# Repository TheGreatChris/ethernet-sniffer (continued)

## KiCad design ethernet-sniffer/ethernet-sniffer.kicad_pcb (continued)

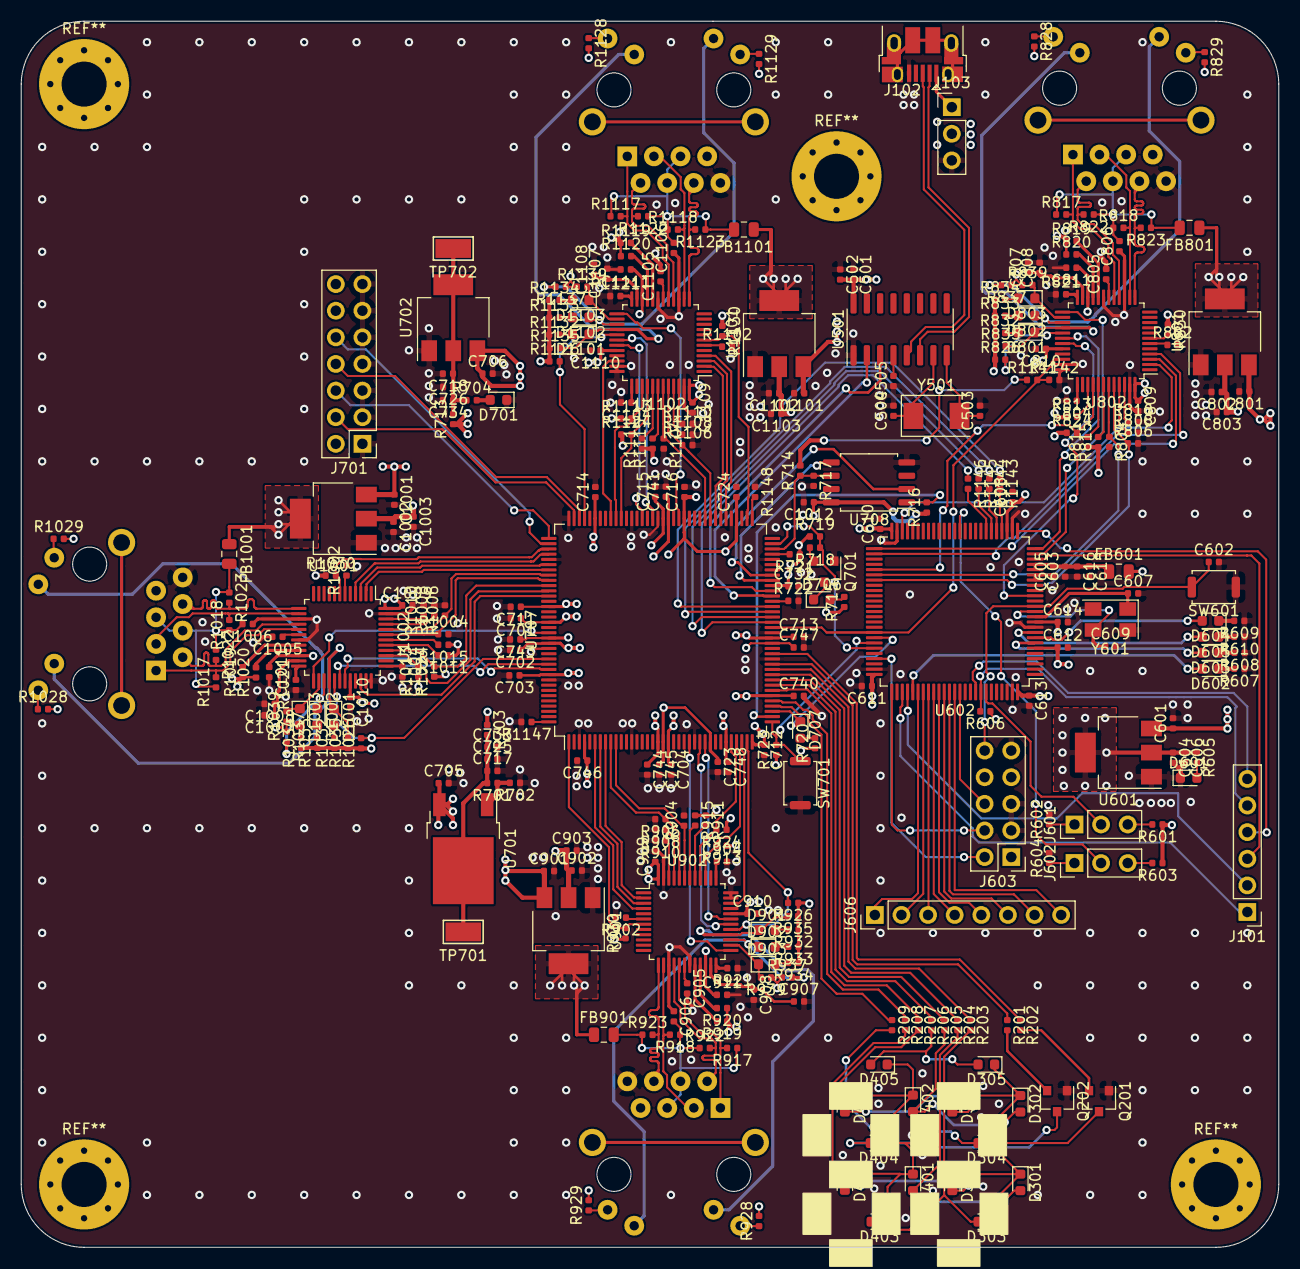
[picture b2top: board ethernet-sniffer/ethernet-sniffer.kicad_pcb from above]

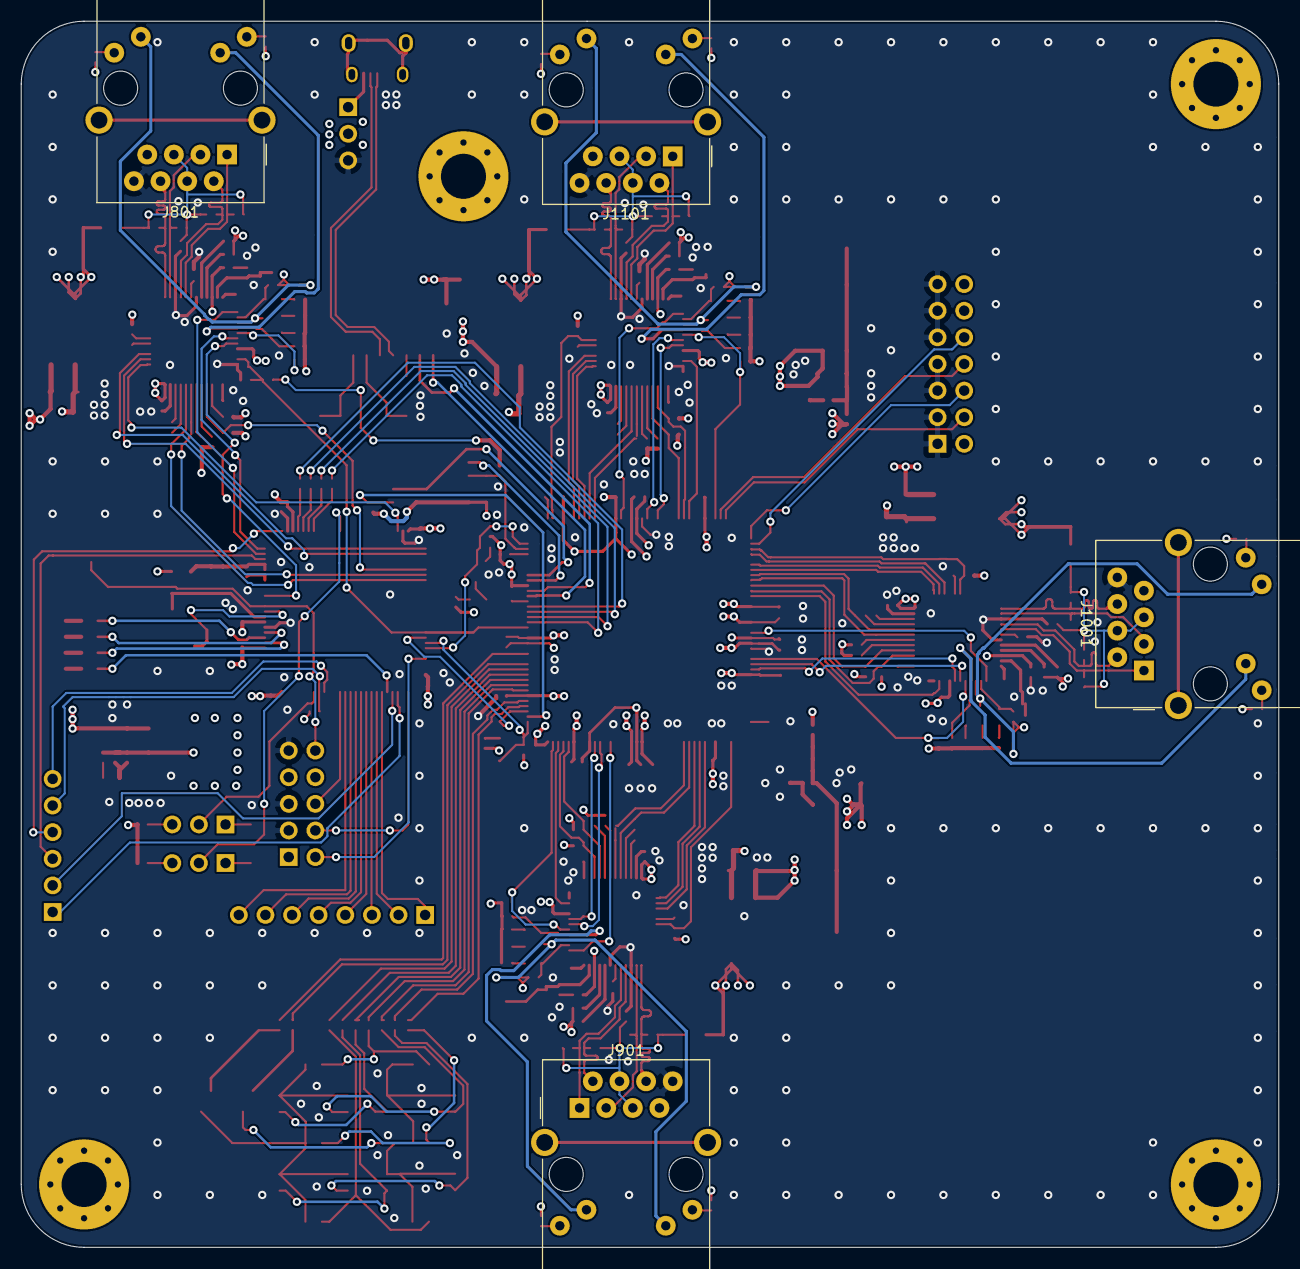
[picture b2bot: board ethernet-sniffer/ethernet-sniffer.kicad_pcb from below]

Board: 4 copper layers, 120.0 x 117.0 mm, 316 parts (4 on the bottom side), 252 nets.

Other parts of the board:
D301, D401: B; LED_0603_1608Metric
D302, D402: C; LED_0603_1608Metric
D303, D403: A; LED_0603_1608Metric
D304, D404: G; LED_0603_1608Metric
D305, D405: D; LED_0603_1608Metric
D306, D406: F; LED_0603_1608Metric
D307, D407: E; LED_0603_1608Metric
Q201, Q202: 2N3904; SOT-23
R201, R202: 1k; R_0402_1005Metric
R203, R204, R205, R206, R207, R208, R209: 200; R_0402_1005Metric

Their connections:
/7seg-display/7SEG-1: R201.1; also elsewhere on the board
/7seg-display/7SEG-2: R202.1; also elsewhere on the board
/7seg-display/7SEG-A: R203.1; also elsewhere on the board
/7seg-display/7SEG-B: R204.1; also elsewhere on the board
/7seg-display/7SEG-C: R205.1; also elsewhere on the board
/7seg-display/7SEG-D: R206.1; also elsewhere on the board
/7seg-display/7SEG-E: R207.1; also elsewhere on the board
/7seg-display/7SEG-F: R208.1; also elsewhere on the board
/7seg-display/7SEG-G: R209.1; also elsewhere on the board
/7seg-display/Digit 1/AK: D301.1, D302.1, D303.1, D304.1, D305.1, D306.1, D307.1, Q201.3
/7seg-display/Digit 1/AN: D303.2, D403.2, R203.2
/7seg-display/Digit 1/BA: D301.2, D401.2, R204.2
/7seg-display/Digit 1/CA: D302.2, D402.2, R205.2
/7seg-display/Digit 1/DA: D305.2, D405.2, R206.2
/7seg-display/Digit 1/EA: D307.2, D407.2, R207.2
/7seg-display/Digit 1/FA: D306.2, D406.2, R208.2
/7seg-display/Digit 1/GA: D304.2, D404.2, R209.2
/7seg-display/Digit 2/AK: D401.1, D402.1, D403.1, D404.1, D405.1, D406.1, D407.1, Q202.3
GNDD: Q201.1, Q202.1; also elsewhere on the board
unnamed: Q201.2, R202.2
unnamed: Q202.2, R201.2

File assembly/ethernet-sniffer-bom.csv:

Comment,Designator,Footprint,LCSC Part #
100n,"C501,C505,C608,C610,C611,C612,C613,C602,C804,C805,C807,C803,C806,C809,C810,C811,C904,C905,C907,C903,C906,C909,C910,C911,C1104,C1105,C1107,C1103,C1106,C1109,C1110,C1111,C741,C743,C745,C747,C702,C704,C712,C713,C715,C701,C703,C711,C714,C716,C724,C732,C740,C744,C746,C748,C723,C1012,C1004,C1005,C1007,C1003,C1006,C1009,C1010,C1011",Capacitor_SMD:C_0402_1005Metric,C1525
10n,"C502,C615,C605",Capacitor_SMD:C_0402_1005Metric,C15195
33p,"C504,C503",Capacitor_SMD:C_0402_1005Metric,C1562
10u,"C601,C604,C808,C801,C908,C901,C1108,C1101,C717,C718,C1008,C1001",Capacitor_SMD:C_0402_1005Metric,C15525
1u,"C606,C616,C603,C802,C902,C1102,C1002",Capacitor_SMD:C_0402_1005Metric,C52923
12p,"C607,C609",Capacitor_SMD:C_0402_1005Metric,C1547
4u7,"C614,C705,C725,C706,C726",Capacitor_SMD:C_0402_1005Metric,C23733
470n,"C733,C734",Capacitor_SMD:C_0402_1005Metric,C47339
B,"D301,D401",LED_SMD:LED_0603_1608Metric,C2286
C,"D302,D402",LED_SMD:LED_0603_1608Metric,C2286
A,"D303,D403",LED_SMD:LED_0603_1608Metric,C2286
G,"D304,D404",LED_SMD:LED_0603_1608Metric,C2286
D,"D305,D405",LED_SMD:LED_0603_1608Metric,C2286
F,"D306,D406",LED_SMD:LED_0603_1608Metric,C2286
E,"D307,D407",LED_SMD:LED_0603_1608Metric,C2286
LED STM POW,D601,LED_SMD:LED_0603_1608Metric,C2286
LED_Small,"D602,D603,D604,D605,D701",LED_SMD:LED_0603_1608Metric,C2286
INIT,"D707,D706",LED_SMD:LED_0603_1608Metric,C2286
LINK,"D801,D901,D1101,D1001",LED_SMD:LED_0603_1608Metric,C2286
SPEED,"D802,D902,D1102,D1002",LED_SMD:LED_0603_1608Metric,C2286
ACT,"D803,D903,D1103,D1003",LED_SMD:LED_0603_1608Metric,C2286
Bead,"FB601,FB801,FB901,FB1101,FB1001",Inductor_SMD:L_0805_2012Metric,C1017
2N3904,"Q202,Q201,Q701",Package_TO_SOT_SMD:SOT-23,C18536
1k,"R201,R202,R1143,R1144,R1145,R1146",Resistor_SMD:R_0402_1005Metric,C11702
200,"R203,R204,R205,R206,R207,R208,R209,R605,R607,R608,R609,R610,R832,R833,R834,R828,R829,R932,R933,R934,R928,R929,R1132,R1133,R1134,R1128,R1129,R704,R720,R715,R716,R1032,R1033,R1034,R1028,R1029",Resistor_SMD:R_0402_1005Metric,C25087
10k,"R602,R601,R604,R603,R718",Resistor_SMD:R_0402_1005Metric,C25744
2k2,"R606,R819,R820,R802,R804,R806,R808,R810,R811,R813,R815,R824,R826,R830,R835,R837,R839,R919,R920,R902,R904,R906,R908,R910,R911,R913,R915,R924,R926,R930,R935,R937,R939,R1119,R1120,R1102,R1104,R1106,R1108,R1110,R1111,R1113,R1115,R1124,R1126,R1130,R1135,R1137,R1139,R719,R721,R722,R723,R1147,R1148,R1019,R1020,R1002,R1004,R1006,R1008,R1010,R1011,R1013,R1015,R1024,R1026,R1030,R1035,R1037,R1039",Resistor_SMD:R_0402_1005Metric,C25879
0,"R701,R703,R713",Resistor_SMD:R_0402_1005Metric,C17168
1M,R702,Resistor_SMD:R_0402_1005Metric,C26083
100,"R717,R714,R1141,R1142",Resistor_SMD:R_0402_1005Metric,C25076
50,"R818,R823,R817,R822,R918,R923,R917,R922,R1118,R1123,R1117,R1122,R1018,R1023,R1017,R1022",Resistor_SMD:R_0402_1005Metric,C25120
4k87,"R821,R921,R1121,R1021",Resistor_SMD:R_0402_1005Metric,C25900
CH340G,U501,Package_SO:SOIC-16_3.9x9.9mm_P1.27mm,C14267
AMS1117-3.3,"U601,U801,U901,U1101,U702,U1001",Package_TO_SOT_SMD:SOT-223-3_TabPin2,C6186
STM32F107VCTx,U602,Package_QFP:LQFP-100_14x14mm_P0.5mm,C8315
LM317_3PinPackage,U701,Package_TO_SOT_SMD:TO-252-2,C75510
XC6SLX9-TQG144,U707,Package_QFP:LQFP-144_20x20mm_P0.5mm,C27408
W25Q128JVS,U708,Package_SO:SOIC-8_5.23x5.23mm_P1.27mm,C97521
DP83848C,"U802,U902,U1102,U1002",Package_QFP:LQFP-48_7x7mm_P0.5mm,C16688
12MHz,Y501,Crystal:Crystal_SMD_0603-2Pin_6.0x3.5mm,C9002
25MHz,Y601,Crystal:Crystal_SMD_5032-4Pin_5.0x3.2mm,C9006

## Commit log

2020-06-03 Add files via upload
    Initial commit
2020-06-04 Add files via upload
    Added PHY1-3
2020-06-04 Add files via upload
    Added again in the right folder this time hopefully
2020-06-23 Cleanup
2020-06-23 v0.01
2020-06-25 PCB layout 90% finished
